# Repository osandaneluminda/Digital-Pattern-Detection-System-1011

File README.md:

# Digital Pattern Detection System Design – 1011

## Project Overview

The **Digital Pattern Detection System** is a synchronous digital system designed to generate, transmit, and detect a specific four-bit binary sequence.

The assigned pattern for this project is **1011**.

The system consists of three main functional modules:

1. Random Pattern Generator
2. Parallel-In Serial-Out (PISO) Shift Register
3. Finite State Machine (FSM) Pattern Detector

The modules operate using a common clock signal. The generated four-bit data is loaded into the PISO register and transmitted serially to the FSM, which detects the assigned sequence 1011.

## System Architecture

The overall data flow is:

**Random Pattern Generator → PISO Shift Register → FSM Pattern Detector → Detection Output**

### 1. Random Pattern Generator

- Generates four-bit pseudo-random binary data.
- Uses D-type flip-flops and XOR feedback logic.
- Requires a non-zero initial state.

### 2. PISO Shift Register

- Uses four D-type flip-flop stages.
- Loads four-bit parallel data.
- Shifts the stored data serially according to the clock.
- Sends serial data to the FSM detector.

### 3. FSM Pattern Detector

- Implements a four-state Mealy finite state machine.
- Uses two state bits.
- Detects the binary sequence 1011.
- Activates the detection output when the complete pattern is received.

## FSM Design

The assigned sequence is:

`1011`

The FSM uses the following state encoding:

| State | Encoding | Description |
|---|---|---|
| S0 | 00 | No relevant pattern matched |
| S1 | 01 | Sequence 1 matched |
| S2 | 10 | Sequence 10 matched |
| S3 | 11 | Sequence 101 matched |

The detection output becomes HIGH when the FSM is in state S3 and receives input 1.

### Boolean Expressions

The simplified next-state equations are:

```text
D0 = X

D1 = Q0X' + Q1Q0'X

DETECT = Q1Q0X
```

Where:
- Q1 and Q0 are the present-state bits.
- X is the serial input.
- D1 and D0 are the next-state inputs.

## Hardware and Components

The design uses digital logic components including:

- D-type flip-flops (74HC74)
- XOR gates
- AND gates (74HC08)
- OR gates (74HC32)
- NOT gates (74HC04)
- Resistors
- LEDs
- Capacitors
- Clock source
- Power supply and connectors

The exact component selection and connections should follow the final circuit schematic.

## Design and Simulation Tools

- Proteus Design Suite – circuit design and simulation
- KiCad – schematic capture and PCB design

## Simulation and Testing

The project includes simulation and testing of:

- Random pattern generation
- PISO parallel loading
- PISO serial shifting
- FSM pattern detection
- Incorrect pattern testing
- Complete system integration
- Clock and detection-output timing waveforms

The integrated system was observed using the Proteus oscilloscope.

### Oscilloscope Signals

- Yellow – Common clock signal
- Blue – PISO serial output
- Pink – FSM detection output

The detection output changes from LOW to HIGH when the complete sequence is detected.

## PCB Design

PCB layouts were developed using KiCad for the following functional blocks:

1. Random Pattern Generator
2. PISO Shift Register
3. FSM Pattern Detector (1011)

The PCB design includes component footprints, connectors, resistors, capacitors, and routed tracks.

## Project Documentation

The complete project report includes:

- System architecture
- FSM state diagram and transition table
- Boolean expressions and Karnaugh maps
- Logic gate implementation
- Proteus circuit simulation
- Oscilloscope timing waveforms
- KiCad PCB layouts
- Testing and analysis

## Project Team

Developed as a group assignment for **Digital Systems Design (IE3004)** at Sri Lanka Institute of Information Technology (SLIIT).

## Key Learning Outcomes

- Sequential logic circuit design
- D-type flip-flop operation
- Shift-register implementation
- Finite State Machine design
- Mealy pattern detection
- Boolean algebra and Karnaugh map simplification
- Clock synchronization
- Digital circuit simulation
- PCB schematic and layout design

---

**Note:** This is an academic digital systems design project developed for educational purposes.

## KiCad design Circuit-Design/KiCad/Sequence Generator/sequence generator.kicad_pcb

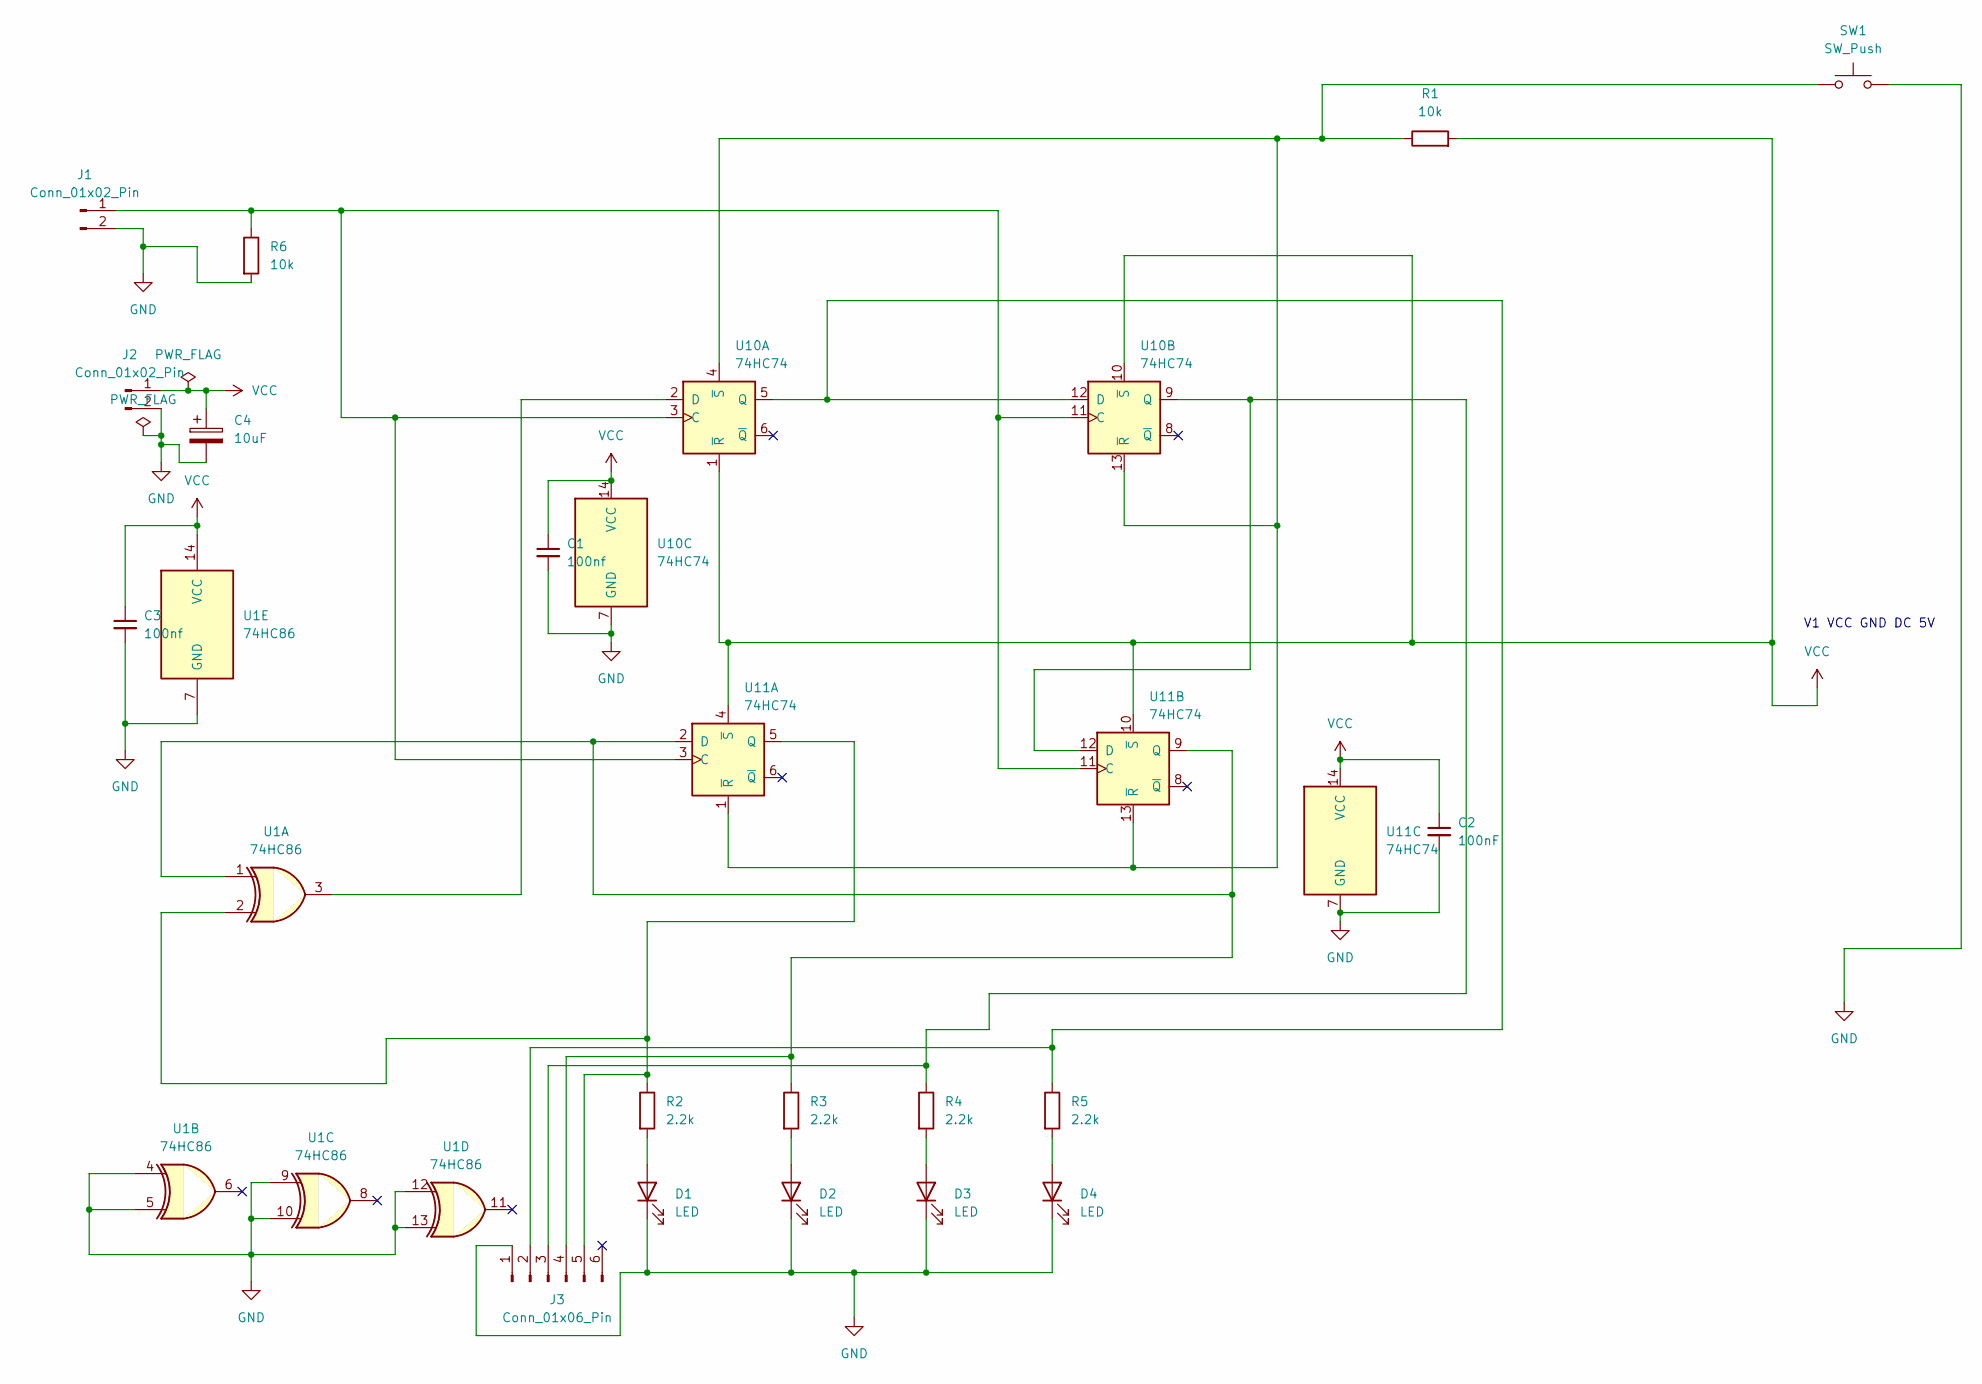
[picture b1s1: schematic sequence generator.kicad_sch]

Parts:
C1, C3: 100nf; C_Disc_D5.0mm_W2.5mm_P5.00mm
C2: 100nF; C_Disc_D5.0mm_W2.5mm_P5.00mm
C4: 10uF; C_Disc_D5.0mm_W2.5mm_P5.00mm
D1, D2, D3, D4: LED; LED_D5.0mm
J1, J2: Conn_01x02_Pin; PinHeader_1x02_P2.54mm_Vertical
J3: Conn_01x06_Pin; PinHeader_1x06_P2.54mm_Vertical
R1, R6: 10k; R_Axial_DIN0207_L6.3mm_D2.5mm_P10.16mm_Horizontal
R2, R3, R4, R5: 2.2k; R_Axial_DIN0207_L6.3mm_D2.5mm_P10.16mm_Horizontal
SW1: SW_Push; SW_PUSH_6mm
U1: 74HC86; DIP-14_W7.62mm
U10, U11: 74HC74; DIP-14_W7.62mm

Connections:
GND: C1.2, C2.2, C3.2, C4.2, D1.1 (K), D2.1 (K), D3.1 (K), D4.1 (K), J1.2, J2.2, J3.1, R6.2, SW1.2, U1.4, U1.5, U1.7 (GND), U1.9, U1.10, U1.12, U1.13, U10.7 (GND), U11.7 (GND)
unnamed: D1.2 (A), R2.2
unnamed: D2.2 (A), R3.2
unnamed: D3.2 (A), R4.2
unnamed: D4.2 (A), R5.2
unnamed: J1.1, R6.1, U10.3 (C), U10.11 (C), U11.3 (C), U11.11 (C)
unnamed: J3.2, R5.1, U10.5 (Q), U10.12 (D)
unnamed: J3.3, R4.1, U10.9 (Q), U11.12 (D)
unnamed: J3.4, R3.1, U1.1, U11.2 (D), U11.9 (Q)
unnamed: J3.5, R2.1, U1.2, U11.5 (Q)
unnamed: U1.3, U10.2 (D)
unnamed: R1.1, SW1.1, U10.4 (~S), U10.13 (~R), U11.1 (~R), U11.13 (~R)
VCC: C1.1, C2.1, C3.1, C4.1, J2.1, R1.2, U1.14 (VCC), U10.1 (~R), U10.10 (~S), U10.14 (VCC), U11.4 (~S), U11.10 (~S), U11.14 (VCC)

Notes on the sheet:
V1 VCC GND DC 5V

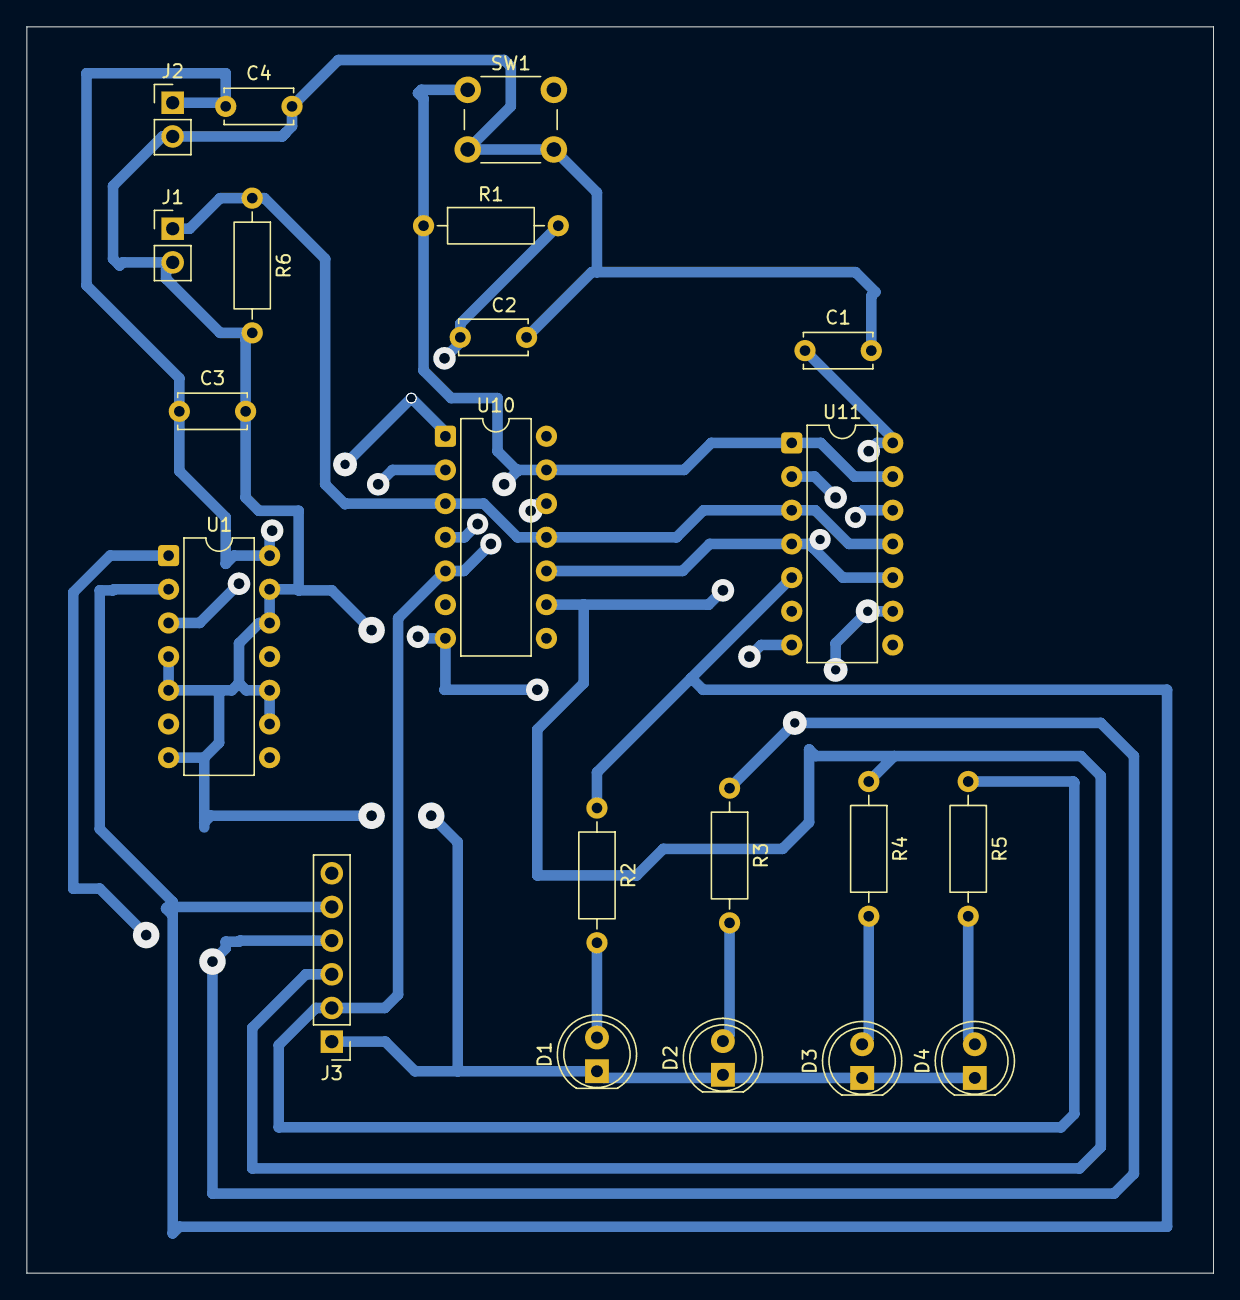
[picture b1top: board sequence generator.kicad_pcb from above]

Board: 2 copper layers, 89.5 x 94.0 mm, 21 parts (0 on the bottom side), 13 nets.

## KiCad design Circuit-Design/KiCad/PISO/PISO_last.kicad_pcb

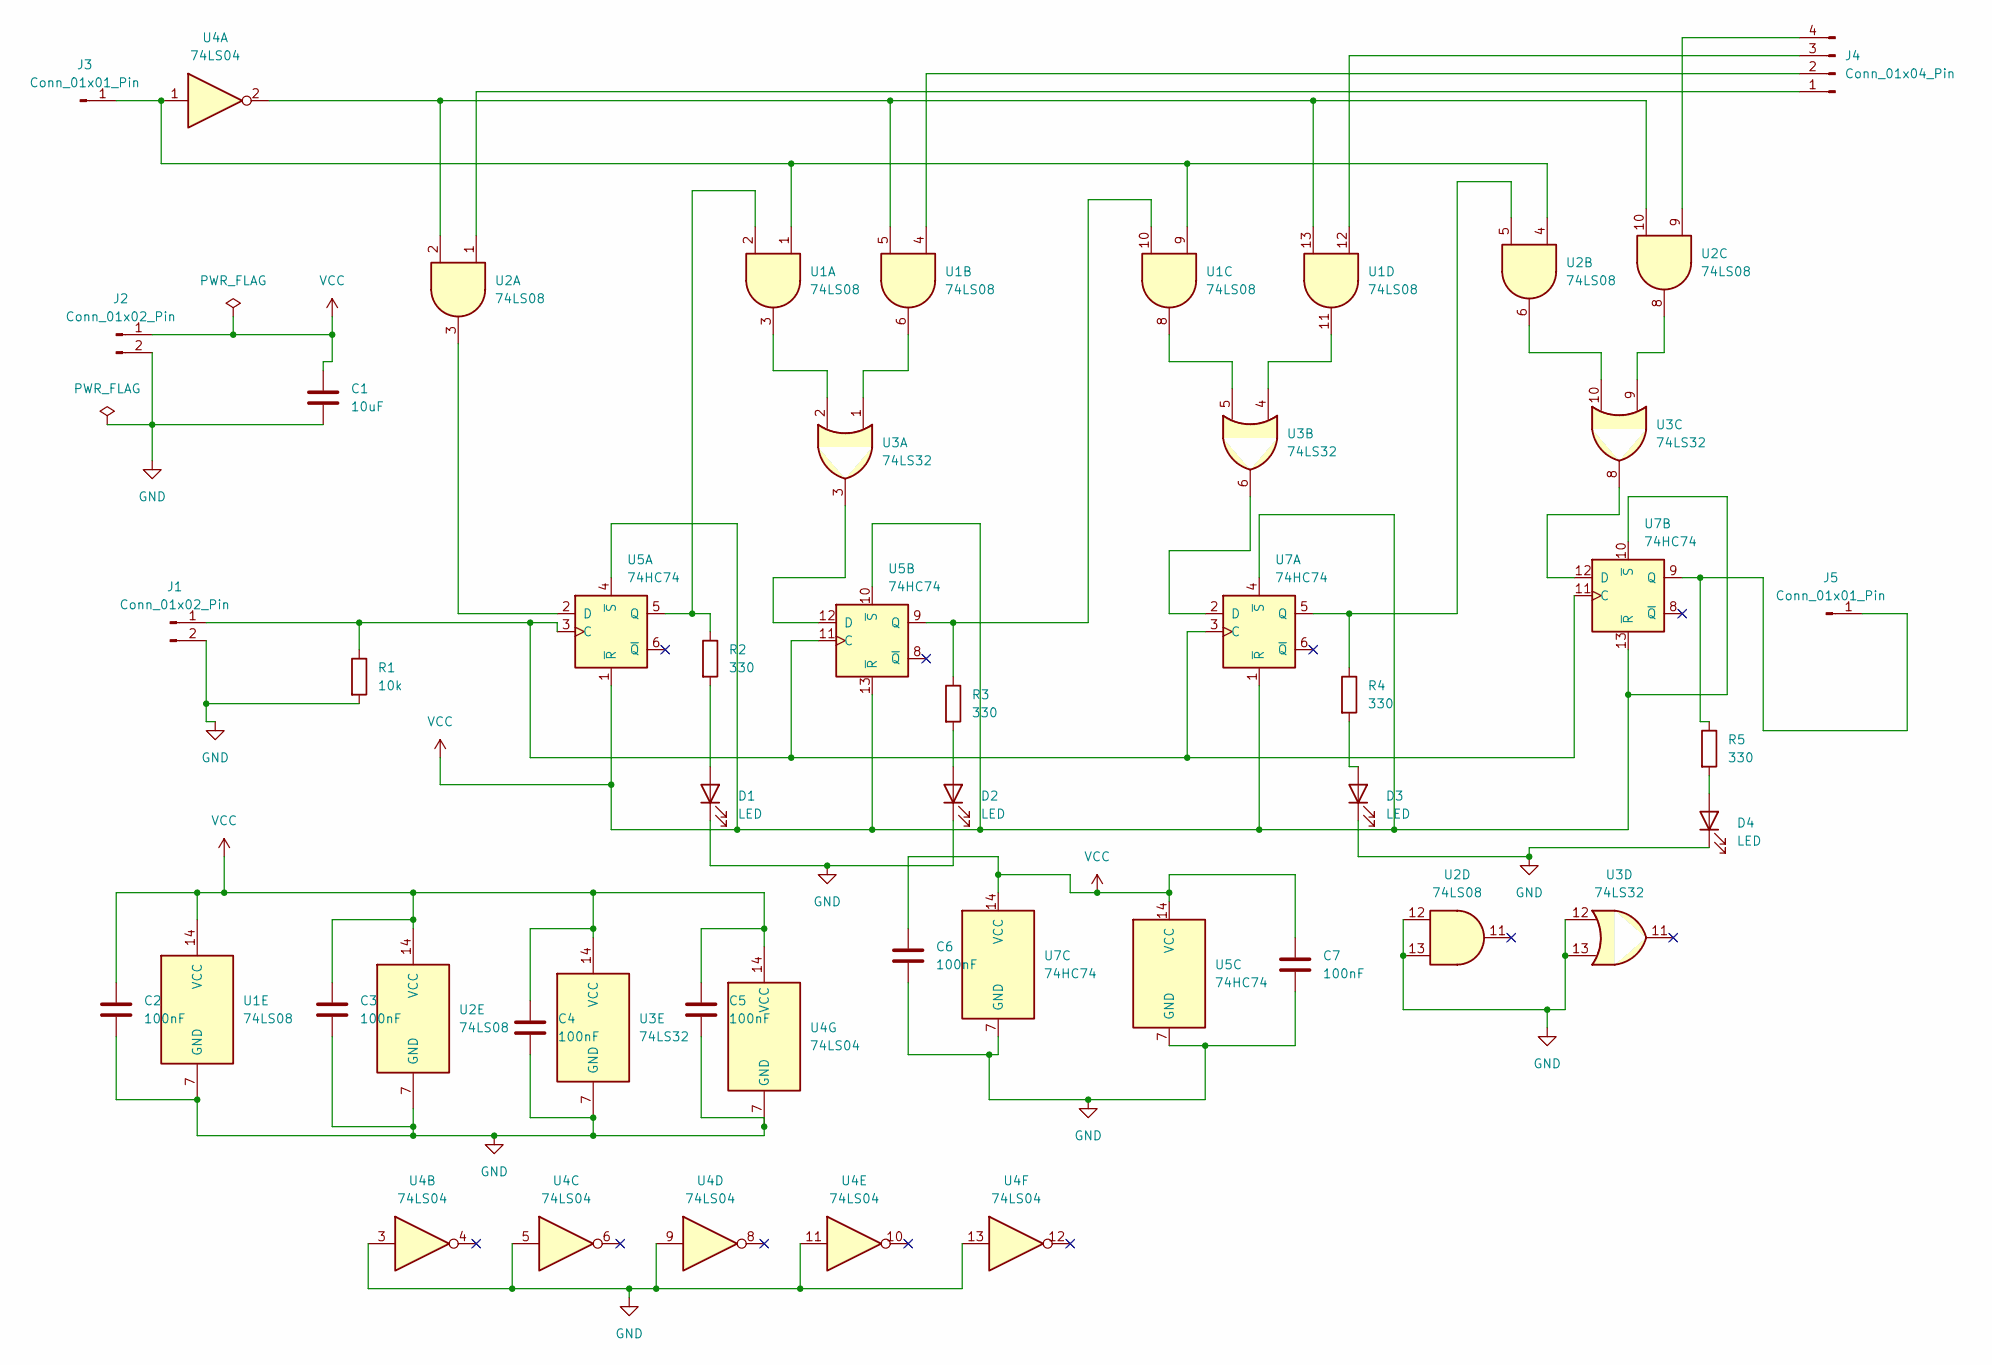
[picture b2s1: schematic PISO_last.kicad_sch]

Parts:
C1: 10uF
C2, C3, C4, C5, C6, C7: 100nF
D1, D2, D3, D4: LED; LED_D5.0mm
J1, J2: Conn_01x02_Pin
J3, J5: Conn_01x01_Pin
J4: Conn_01x04_Pin
R1: 10k
R2, R3, R4, R5: 330; R_Axial_DIN0207_L6.3mm_D2.5mm_P7.62mm_Horizontal
U1, U2: 74LS08
U3: 74LS32
U4: 74LS04
U5, U7: 74HC74

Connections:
GND: C1.2, C2.2, C3.2, C4.2, C5.2, C6.2, C7.2, D1.1 (K), D2.1 (K), D3.1 (K), D4.1 (K), J1.2, J2.2, R1.2, U1.7 (GND), U2.7 (GND), U2.12, U2.13, U3.7 (GND), U3.12, U3.13, U4.3, U4.5, U4.7 (GND), U4.9, U4.11, U4.13, U5.7 (GND), U7.7 (GND)
unnamed: D1.2 (A), R2.2
unnamed: D2.2 (A), R3.2
unnamed: D3.2 (A), R4.2
unnamed: D4.2 (A), R5.2
unnamed: J1.1, R1.1, U5.3 (C), U5.11 (C), U7.3 (C), U7.11 (C)
unnamed: J3.1 (Pin_1_1), U1.1, U1.9, U2.4, U4.1
unnamed: J4.1, U2.1
unnamed: J4.2, U1.4
unnamed: J4.3, U1.12
unnamed: J4.4, U2.9
unnamed: J5.1 (Pin_1_1), R5.1, U7.9 (Q)
unnamed: U1.3, U3.2
unnamed: U1.6, U3.1
unnamed: U1.8, U3.5
unnamed: U1.11, U3.4
unnamed: U1.5, U1.13, U2.2, U2.10, U4.2
unnamed: U2.6, U3.10
unnamed: U2.8, U3.9
unnamed: U2.3, U5.2 (D)
unnamed: R2.1, U1.2, U5.5 (Q)
unnamed: U3.3, U5.12 (D)
unnamed: R3.1, U1.10, U5.9 (Q)
unnamed: U3.6, U7.2 (D)
unnamed: R4.1, U2.5, U7.5 (Q)
unnamed: U3.8, U7.12 (D)
VCC: C1.1, C2.1, C3.1, C4.1, C5.1, C6.1, C7.1, J2.1, U1.14 (VCC), U2.14 (VCC), U3.14 (VCC), U4.14 (VCC), U5.1 (~R), U5.4 (~S), U5.10 (~S), U5.13 (~R), U5.14 (VCC), U7.1 (~R), U7.4 (~S), U7.10 (~S), U7.13 (~R), U7.14 (VCC)

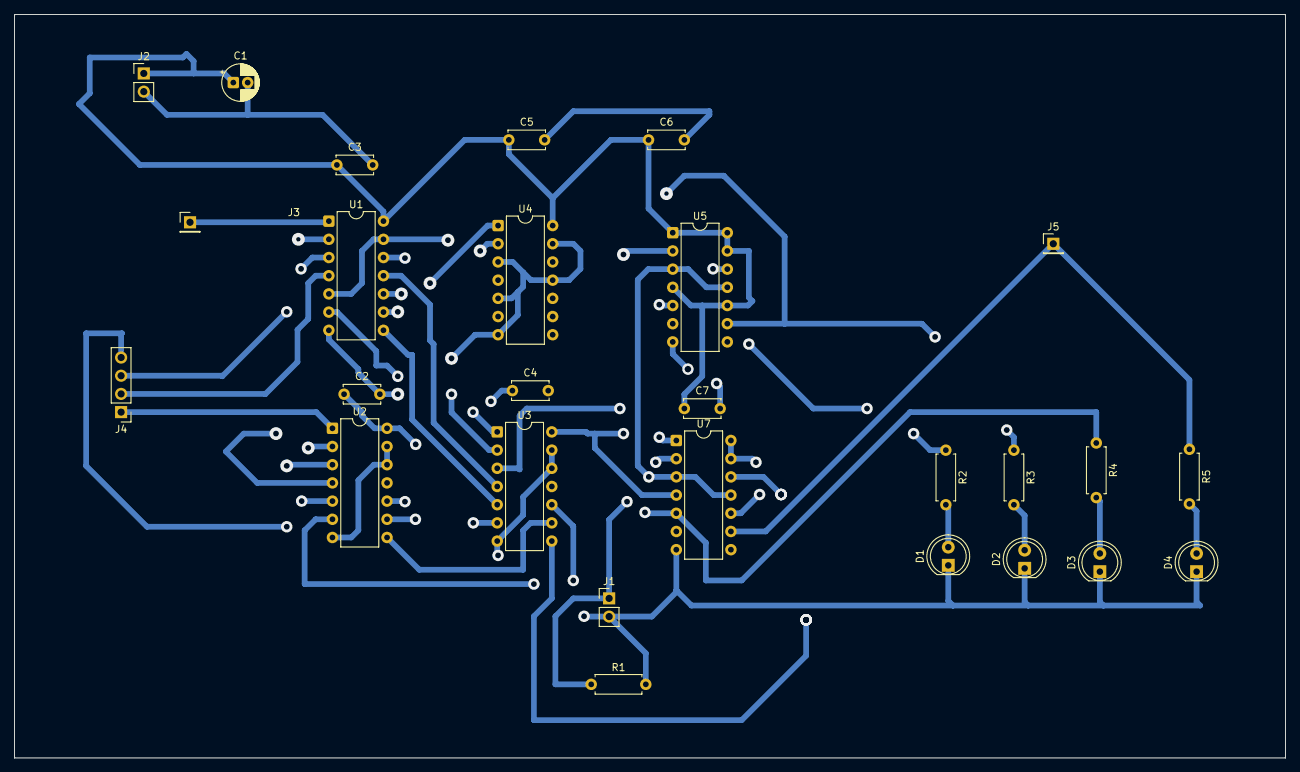
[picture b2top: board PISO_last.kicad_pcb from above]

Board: 2 copper layers, 177.4 x 103.8 mm, 27 parts (0 on the bottom side), 27 nets.

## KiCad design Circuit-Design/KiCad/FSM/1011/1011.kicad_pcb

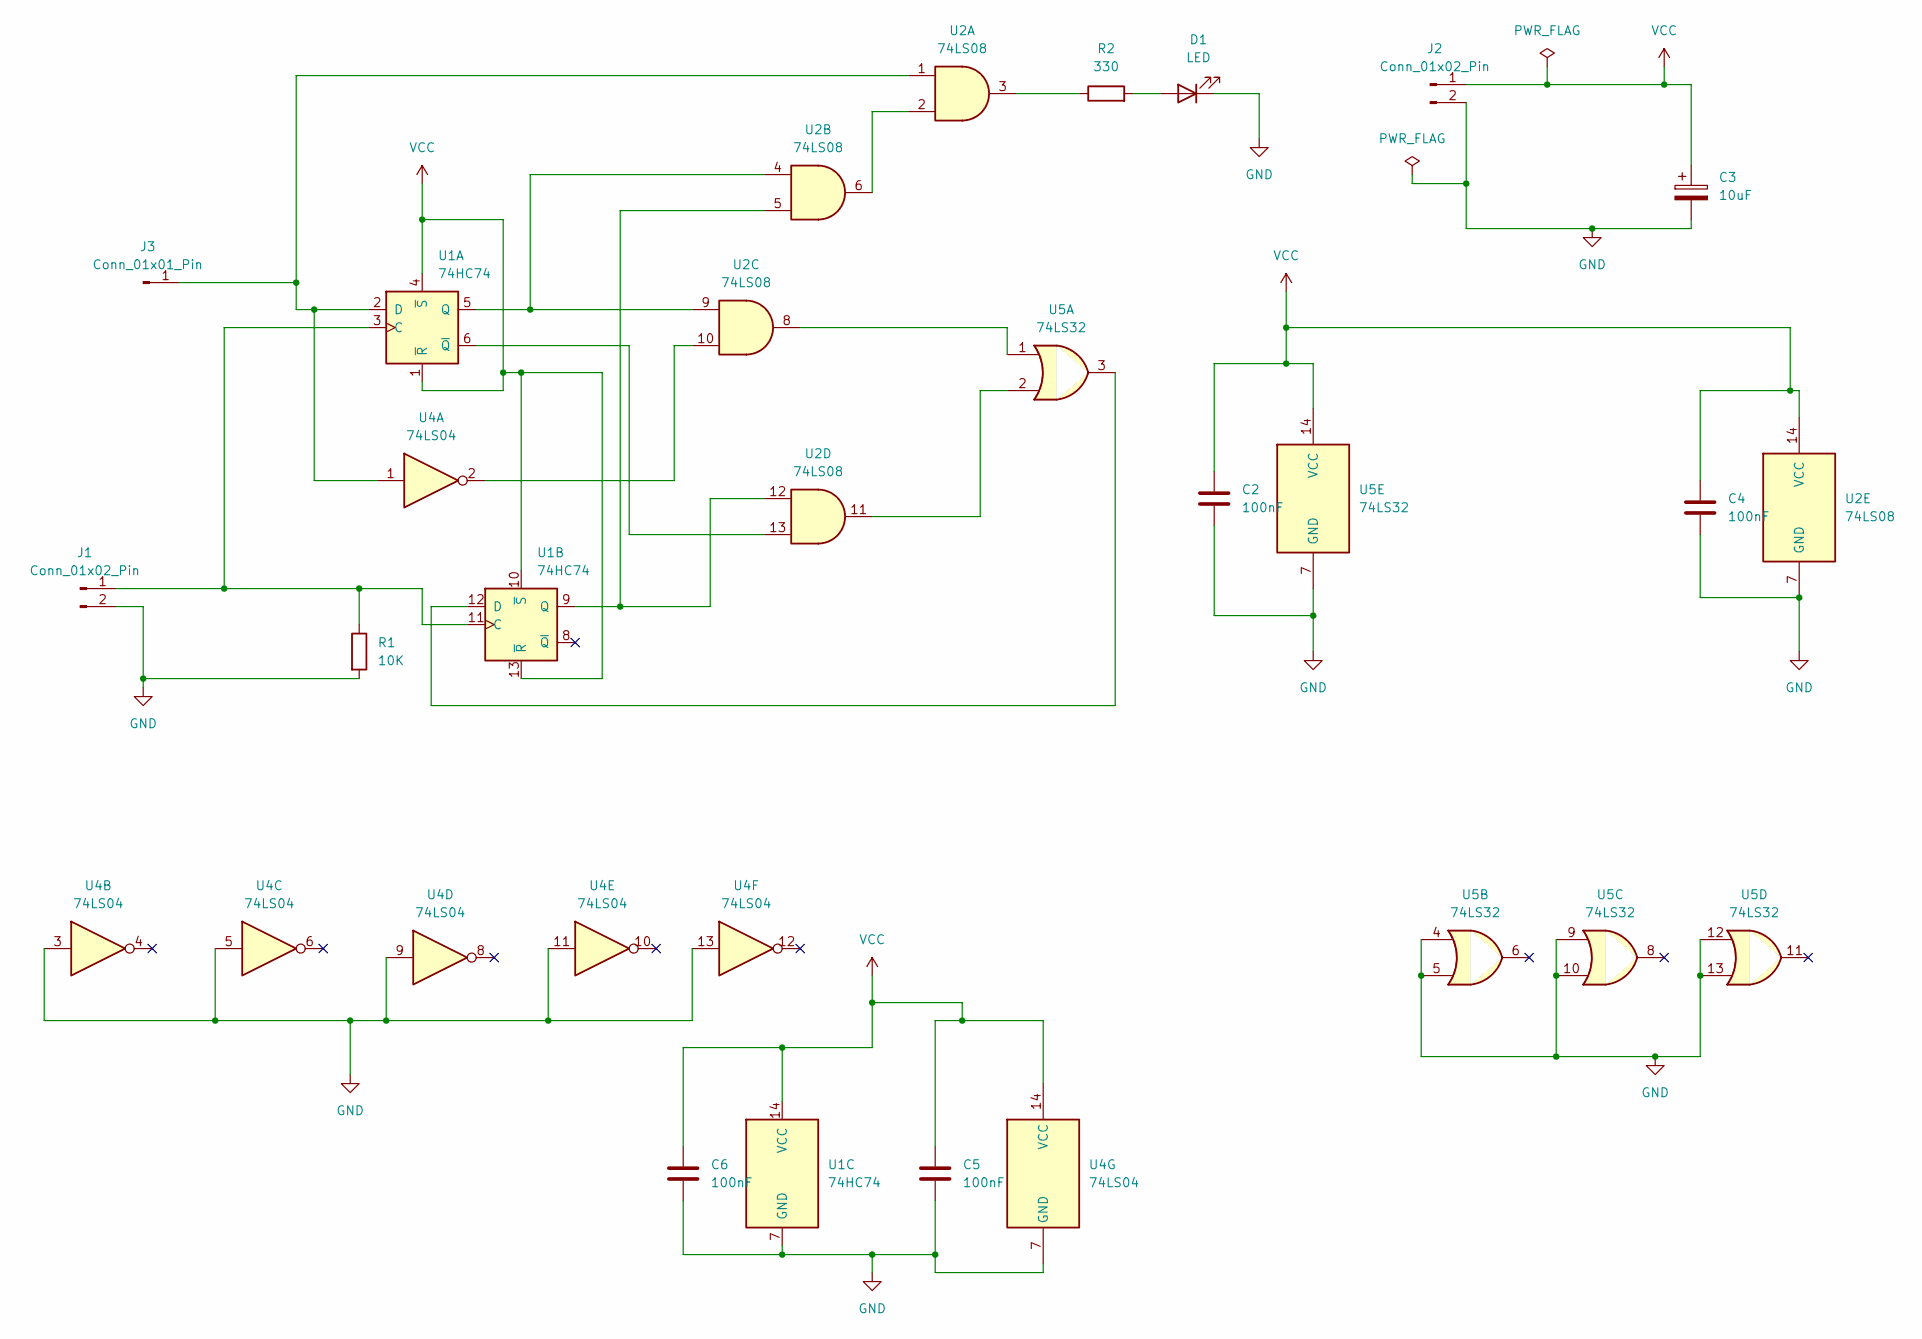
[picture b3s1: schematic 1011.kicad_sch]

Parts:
C2, C4, C5, C6: 100nF; C_Disc_D5.0mm_W2.5mm_P5.00mm
C3: 10uF; CP_Radial_D5.0mm_P2.00mm
D1: LED; LED_D5.0mm
J1, J2: Conn_01x02_Pin; PinHeader_1x02_P2.54mm_Vertical
J3: Conn_01x01_Pin; PinHeader_1x01_P2.54mm_Vertical
R1: 10K; R_Axial_DIN0207_L6.3mm_D2.5mm_P7.62mm_Horizontal
R2: 330; R_Axial_DIN0207_L6.3mm_D2.5mm_P7.62mm_Horizontal
U1: 74HC74; DIP-14_W7.62mm
U2: 74LS08; DIP-14_W7.62mm
U4: 74LS04; DIP-14_W7.62mm
U5: 74LS32; DIP-14_W7.62mm

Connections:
GND: C2.2, C3.2, C4.2, C5.2, C6.2, D1.1 (K), J1.2, J2.2, R1.2, U1.7 (GND), U2.7 (GND), U4.3, U4.5, U4.7 (GND), U4.9, U4.11, U4.13, U5.4, U5.5, U5.7 (GND), U5.9, U5.10, U5.12, U5.13
unnamed: D1.2 (A), R2.2
unnamed: J1.1, R1.1, U1.3 (C), U1.11 (C)
unnamed: J3.1 (Pin_1_1), U1.2 (D), U2.1, U4.1
unnamed: R2.1, U2.3
unnamed: U1.5 (Q), U2.4, U2.9
unnamed: U1.6 (~Q), U2.13
unnamed: U1.12 (D), U5.3
unnamed: U1.9 (Q), U2.5, U2.12
unnamed: U2.2, U2.6
unnamed: U2.8, U5.1
unnamed: U2.10, U4.2
unnamed: U2.11, U5.2
VCC: C2.1, C3.1, C4.1, C5.1, C6.1, J2.1, U1.1 (~R), U1.4 (~S), U1.10 (~S), U1.13 (~R), U1.14 (VCC), U2.14 (VCC), U4.14 (VCC), U5.14 (VCC)

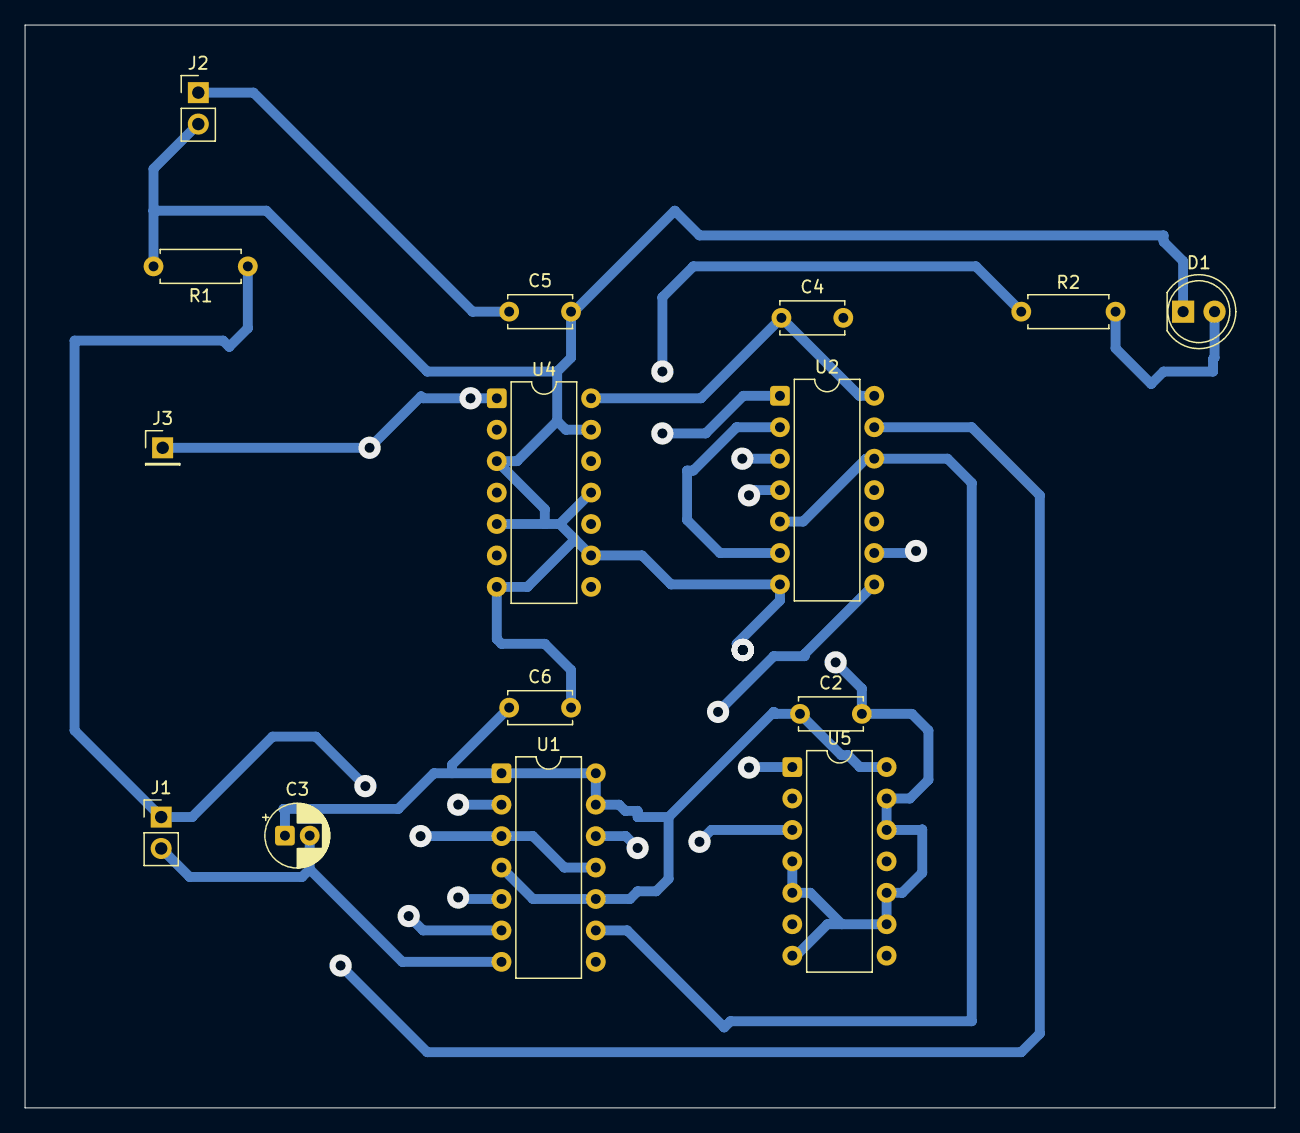
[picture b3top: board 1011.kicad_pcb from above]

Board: 2 copper layers, 101.0 x 87.5 mm, 15 parts (0 on the bottom side), 14 nets.
